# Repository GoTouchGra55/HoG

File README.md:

# HoG FC

This repository includes the custom flight controller, a PDU, and a telemetry unit that is to be used in the drone.

# Overviews

Hand of God flight controller is a custom STM32-based drone flight computer intended to be deployed for humanitarian aid missions.

See [FC Schematics](Kicad/FC/HoG.pdf)
See [Telemetry Schematics](Kicad/Telemetry/HoG_Telemetry.pdf)

## Routing

# Features

## Core

- STM32H743 Cortex-M7 MCU
- Up to 480 MHz CPU clock
- MicroSD storage
- SWD debugging
- USB-C
- Barometer
- Gyroscope & Accelerometer
- GPS/GNSS

## Power

The flight controller board provides dedicated:

- 22.2 V rail (6s nominal)
- 5 V rail
- 3.3 V rail

## Rough BOM

| #   | Item           |        Cost | Supplier    |
| --- | -------------- | ----------: | ----------- |
| 1   | PCBs           |     $299.96 | JLCPCB      |
| 2   | SMD Resistors  |       $8.35 | Daraz Nepal |
| 3   | SMD Capacitors |       $7.98 | Daraz Nepal |
|     | **Total**      | **$316.29** |             |

# Authors 👥

Shaurya (Electronics)  
Contact: [E-mail](shauryatamang.dev@gmail.com)

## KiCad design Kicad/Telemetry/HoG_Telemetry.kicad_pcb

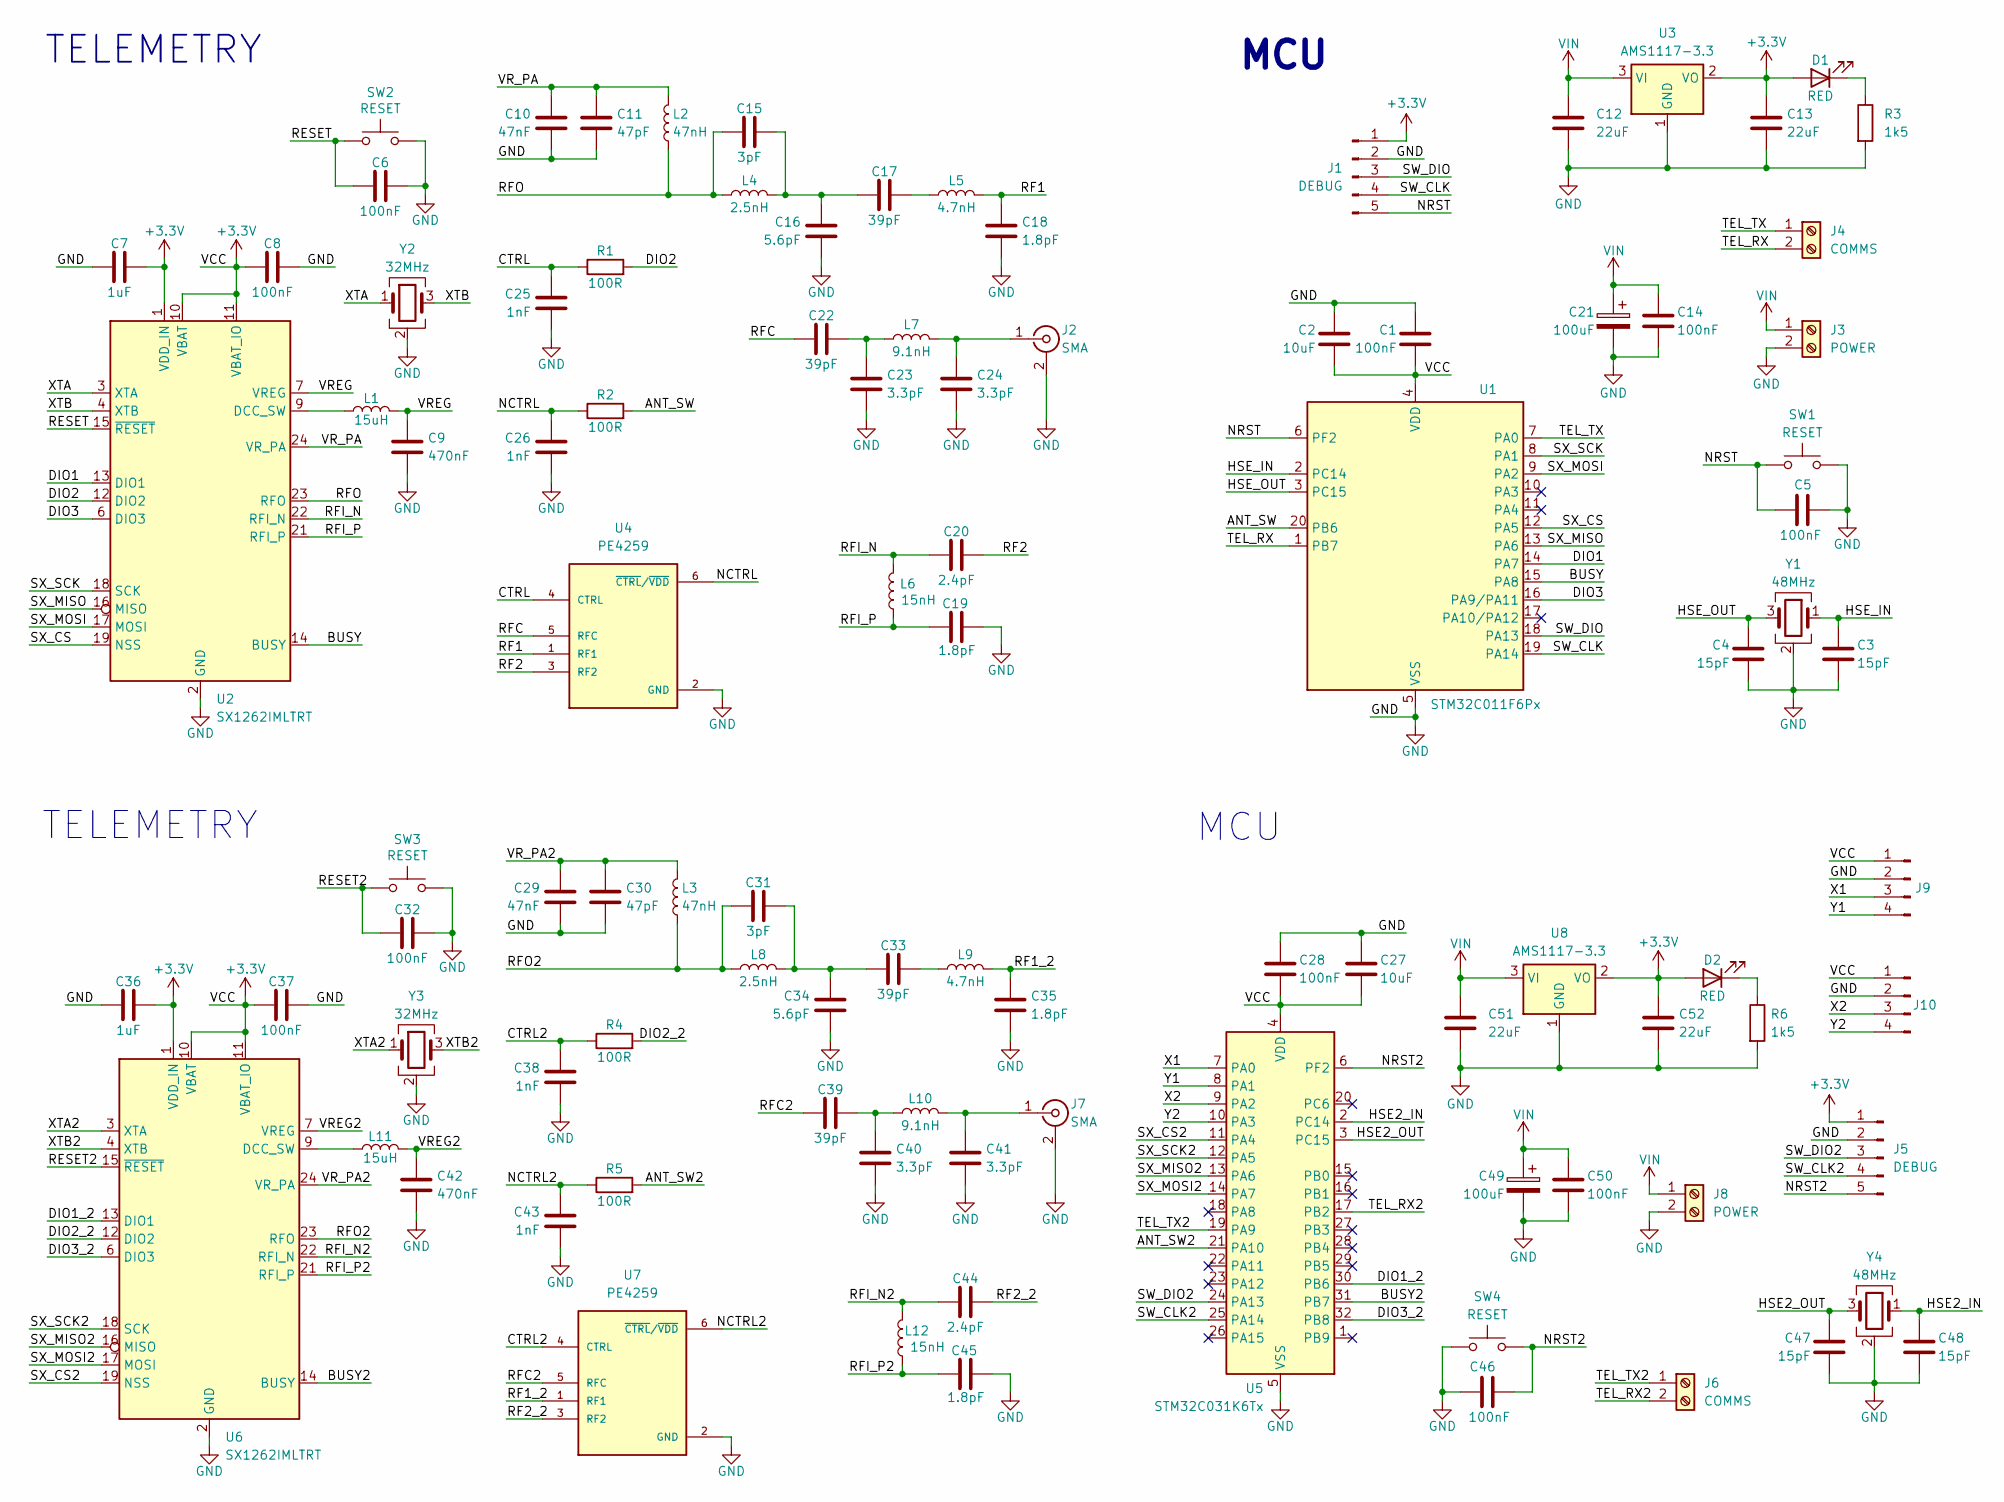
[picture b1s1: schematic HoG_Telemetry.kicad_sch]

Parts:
C1, C5, C6, C8, C14, C28, C32, C37, C46, C50: 100nF; C_0402_1005Metric
C2, C27: 10uF; C_0603_1608Metric
C3, C4, C47, C48: 15pF; C_0402_1005Metric
C7, C36: 1uF; C_0603_1608Metric
C9, C42: 470nF; C_0402_1005Metric
C10, C29: 47nF; C_0402_1005Metric
C11, C30: 47pF; C_0402_1005Metric
C12, C13, C51, C52: 22uF; C_0805_2012Metric
C15, C31: 3pF; C_0402_1005Metric
C16, C34: 5.6pF; C_0402_1005Metric
C17, C22, C33, C39: 39pF; C_0402_1005Metric
C18, C19, C35, C45: 1.8pF; C_0402_1005Metric
C20, C44: 2.4pF; C_0402_1005Metric
C21, C49: 100uF; C_0603_1608Metric
C23, C24, C40, C41: 3.3pF; C_0402_1005Metric
C25, C26, C38, C43: 1nF; C_0402_1005Metric
D1, D2: RED; LED_0603_1608Metric
J1, J5: DEBUG; PinHeader_1x05_P2.54mm_Horizontal
J2, J7: SMA; SMA_Amphenol_132134-10_Vertical
J3, J8: POWER; PinHeader_1x02_P2.54mm_Horizontal
J4, J6: COMMS; PinHeader_1x02_P2.54mm_Horizontal
J9, J10: Conn_01x04_Pin; JST_EH_B4B-EH-A_1x04_P2.50mm_Vertical
L1, L11: 15uH; L_0805_2012Metric
L2, L3: 47nH; L_0402_1005Metric
L4, L8: 2.5nH; L_0402_1005Metric
L5, L9: 4.7nH; L_0402_1005Metric
L6, L12: 15nH; L_0402_1005Metric
L7, L10: 9.1nH; L_0402_1005Metric
R1, R2, R4, R5: 100R; R_0402_1005Metric
R3, R6: 1k5; R_0402_1005Metric
SW1, SW2, SW3, SW4: RESET; SW_Push_SPST_NO_Alps_SKRK
U1: STM32C011F6Px; TSSOP-20_4.4x6.5mm_P0.65mm
U2, U6: SX1262IMLTRT; QFN-24-1EP_4x4mm_P0.5mm_EP2.6x2.6mm
U3, U8: AMS1117-3.3; SOT-223-3_TabPin2
U4, U7: PE4259; SOT65P215X110-6N
U5: STM32C031K6Tx; LQFP-32_7x7mm_P0.8mm
Y1, Y4: 48MHz; Crystal_SMD_3225-4Pin_3.2x2.5mm
Y2, Y3: 32MHz; Crystal_SMD_3225-4Pin_3.2x2.5mm

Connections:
+3.3V: C1.2, C2.2, C7.2, C8.1, C13.1, C27.2, C28.2, C36.2, C37.1, C52.1, D1.2 (A), D2.2 (A), J1.1, J5.1, J9.1, J10.1, U1.4 (VDD), U2.1 (VDD_IN), U2.10 (VBAT), U2.11 (VBAT_IO), U3.2 (VO), U5.4 (VDD), U6.1 (VDD_IN), U6.10 (VBAT), U6.11 (VBAT_IO), U8.2 (VO)
/ANT_SW: R2.2, U1.20 (PB6)
/ANT_SW2: R5.2, U5.21 (PA10)
/BUSY: U1.15 (PA8), U2.14 (BUSY)
/BUSY2: U5.31 (PB7), U6.14 (BUSY)
/CTRL: C25.1, R1.1, U4.4 (CTRL)
/CTRL2: C38.1, R4.1, U7.4 (CTRL)
/DIO1: U1.14 (PA7), U2.13 (DIO1)
/DIO1_2: U5.30 (PB6), U6.13 (DIO1)
/DIO2: R1.2, U2.12 (DIO2)
/DIO2_2: R4.2, U6.12 (DIO2)
/DIO3: U1.16 (PA9/PA11), U2.6 (DIO3)
/DIO3_2: U5.32 (PB8), U6.6 (DIO3)
/HSE2_IN: C48.1, U5.2 (PC14), Y4.1
/HSE2_OUT: C47.1, U5.3 (PC15), Y4.3
/HSE_IN: C3.1, U1.2 (PC14), Y1.1
/HSE_OUT: C4.1, U1.3 (PC15), Y1.3
/NCTRL: C26.1, R2.1, U4.6 (~CTRL/~VDD)
/NCTRL2: C43.1, R5.1, U7.6 (~CTRL/~VDD)
/NRST: C5.2, J1.5, SW1.2, U1.6 (PF2)
/NRST2: C46.2, J5.5, SW4.2, U5.6 (PF2)
/RESET: C6.2, SW2.2, U2.15 (~RESET)
/RESET2: C32.2, SW3.2, U6.15 (~RESET)
/RF1: C18.1, L5.2, U4.1 (RF1)
/RF1_2: C35.1, L9.2, U7.1 (RF1)
/RF2: C20.2, U4.3 (RF2)
/RF2_2: C44.2, U7.3 (RF2)
/RFC: C22.1, U4.5 (RFC)
/RFC2: C39.1, U7.5 (RFC)
/RFI_N: C20.1, L6.2, U2.22 (RFI_N)
/RFI_N2: C44.1, L12.2, U6.22 (RFI_N)
/RFI_P: C19.1, L6.1, U2.21 (RFI_P)
/RFI_P2: C45.1, L12.1, U6.21 (RFI_P)
/RFO: C15.1, L2.1, L4.1, U2.23 (RFO)
/RFO2: C31.1, L3.1, L8.1, U6.23 (RFO)
/SW_CLK: J1.4, U1.19 (PA14)
/SW_CLK2: J5.4, U5.25 (PA14)
/SW_DIO: J1.3, U1.18 (PA13)
/SW_DIO2: J5.3, U5.24 (PA13)
/SX_CS: U1.12 (PA5), U2.19 (NSS)
/SX_CS2: U5.11 (PA4), U6.19 (NSS)
/SX_MISO: U1.13 (PA6), U2.16 (MISO)
/SX_MISO2: U5.13 (PA6), U6.16 (MISO)
/SX_MOSI: U1.9 (PA2), U2.17 (MOSI)
/SX_MOSI2: U5.14 (PA7), U6.17 (MOSI)
/SX_SCK: U1.8 (PA1), U2.18 (SCK)
/SX_SCK2: U5.12 (PA5), U6.18 (SCK)
/TEL_RX: J4.2, U1.1 (PB7)
/TEL_RX2: J6.2, U5.17 (PB2)
/TEL_TX: J4.1, U1.7 (PA0)
/TEL_TX2: J6.1, U5.19 (PA9)
/VREG: C9.1, L1.2, U2.7 (VREG)
/VREG2: C42.1, L11.2, U6.7 (VREG)
/VR_PA: C10.1, C11.1, L2.2, U2.24 (VR_PA)
/VR_PA2: C29.1, C30.1, L3.2, U6.24 (VR_PA)
/X1: J9.3, U5.7 (PA0)
/X2: J10.3, U5.9 (PA2)
/XTA: U2.3 (XTA), Y2.1
/XTA2: U6.3 (XTA), Y3.1
/XTB: U2.4 (XTB), Y2.3
/XTB2: U6.4 (XTB), Y3.3
/Y1: J9.4, U5.8 (PA1)
/Y2: J10.4, U5.10 (PA3)
GND: C1.1, C2.1, C3.2, C4.2, C5.1, C6.1, C7.1, C8.2, C9.2, C10.2, C11.2, C12.2, C13.2, C14.2, C16.2, C18.2, C19.2, C21.2, C23.2, C24.2, C25.2, C26.2, C27.1, C28.1, C29.2, C30.2, C32.1, C34.2, C35.2, C36.1, C37.2, C38.2, C40.2, C41.2, C42.2, C43.2, C45.2, C46.1, C47.2, C48.2, C49.2, C50.2, C51.2, C52.2, J1.2, J2.2 (Ext), J3.2, J5.2, J7.2 (Ext), J8.2, J9.2, J10.2, R3.2, R6.2, SW1.1, SW2.1, SW3.1, SW4.1, U1.5 (VSS), U2.2 (GND), U2.5 (GND), U2.8 (GND), U2.20 (GND), U2.25 (GND), U3.1 (GND), U4.2 (GND), U5.5 (VSS), U6.2 (GND), U6.5 (GND), U6.8 (GND), U6.20 (GND), U6.25 (GND), U7.2 (GND), U8.1 (GND), Y1.2 (G), Y1.4 (G), Y2.2 (G), Y2.4 (G), Y3.2 (G), Y3.4 (G), Y4.2 (G), Y4.4 (G)
unnamed: C15.2, C16.1, C17.1, L4.2
unnamed: C17.2, L5.1
unnamed: C22.2, C23.1, L7.1
unnamed: C31.2, C33.1, C34.1, L8.2
unnamed: C33.2, L9.1
unnamed: C39.2, C40.1, L10.1
unnamed: D1.1 (K), R3.1
unnamed: D2.1 (K), R6.1
unnamed: C24.1, J2.1 (In), L7.2
unnamed: C41.1, J7.1 (In), L10.2
unnamed: L1.1, U2.9 (DCC_SW)
unnamed: L11.1, U6.9 (DCC_SW)
VIN: C12.1, C14.1, C21.1, C49.1, C50.1, C51.1, J3.1, J8.1, U3.3 (VI), U8.3 (VI)

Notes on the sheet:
MCU
TELEMETRY

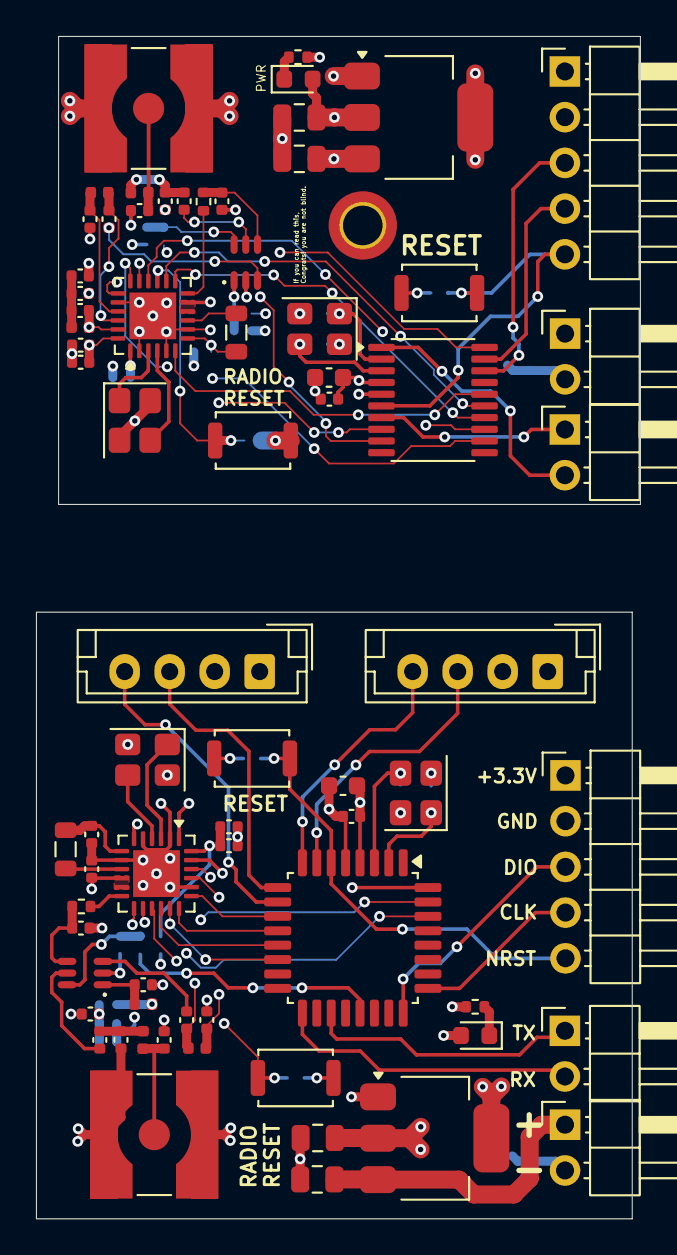
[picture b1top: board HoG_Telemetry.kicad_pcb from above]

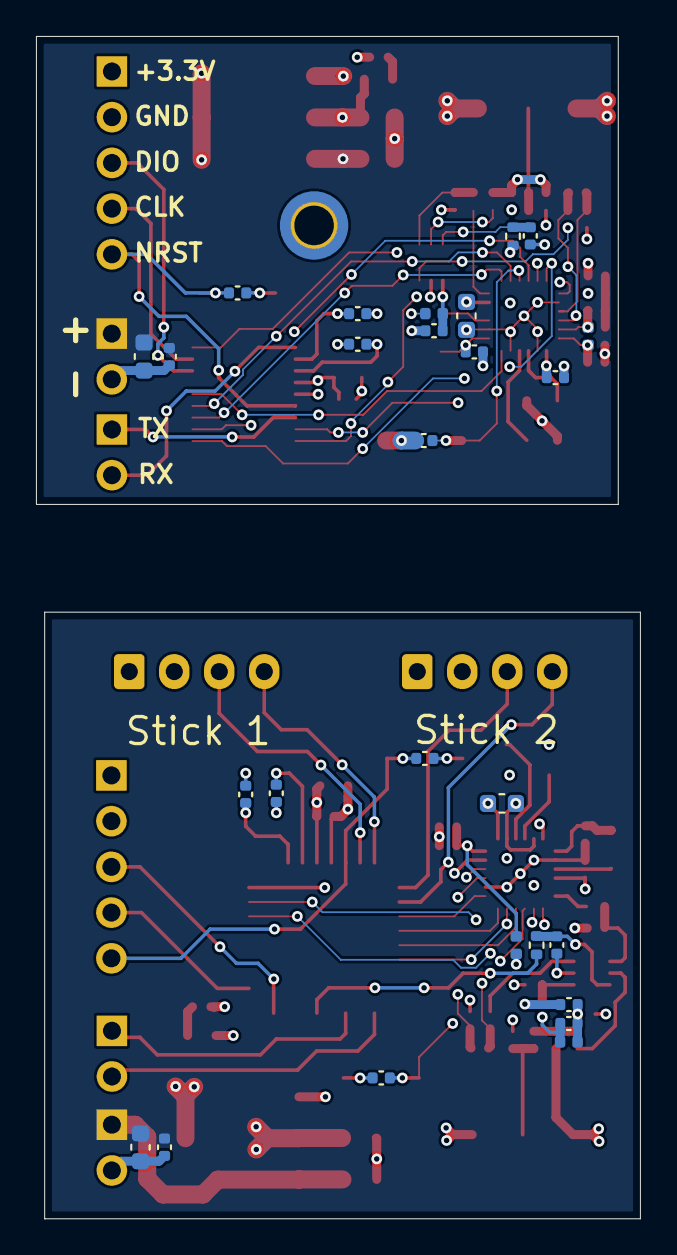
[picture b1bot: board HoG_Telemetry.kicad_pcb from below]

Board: 4 copper layers, 33.6 x 65.7 mm, 98 parts (27 on the bottom side), 77 nets.

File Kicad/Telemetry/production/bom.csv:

Designator,Footprint,Quantity,Value,LCSC Part #
"C1, C14, C28, C32, C37, C46, C5, C50, C6, C8",0402,10,100nF,
"C10, C29",0402,2,47nF,
"C11, C30",0402,2,47pF,
"C12, C13, C51, C52",0805,4,22uF,
"C15, C31",0402,2,3pF,
"C16, C34",0402,2,5.6pF,
"C17, C22, C33, C39",0402,4,39pF,
"C18, C19, C35, C45",0402,4,1.8pF,
"C2, C27",0603,2,10uF,
"C20, C44",0402,2,2.4pF,
"C21, C49",0603,2,100uF,
"C23, C24, C40, C41",0402,4,3.3pF,
"C25, C26, C38, C43",0402,4,1nF,
"C3, C4, C47, C48",0402,4,15pF,
"C36, C7",0603,2,1uF,
"C42, C9",0402,2,470nF,
"D1, D2",0603,2,RED,
"J1, J5",PinHeader_1x05_P2.54mm_Horizontal,2,DEBUG,
"J10, J9",JST_EH_B4B-EH-A_1x04_P2.50mm_Vertical,2,Conn_01x04_Pin,
"J2, J7",SMA_Amphenol_132134-10_Vertical,2,SMA,
"J3, J8",PinHeader_1x02_P2.54mm_Horizontal,2,POWER,
"J4, J6",PinHeader_1x02_P2.54mm_Horizontal,2,COMMS,
"L1, L11",0805,2,15uH,
"L10, L7",0402,2,9.1nH,
"L12, L6",0402,2,15nH,
"L2, L3",0402,2,47nH,
"L4, L8",0402,2,2.5nH,
"L5, L9",0402,2,4.7nH,
"R1, R2, R4, R5",0402,4,100R,
"R3, R6",0402,2,1k5,
"SW1, SW2, SW3, SW4",SW_Push_SPST_NO_Alps_SKRK,4,RESET,
U1,TSSOP-20_4.4x6.5mm_P0.65mm,1,STM32C011F6Px,
"U2, U6",QFN-24-1EP_4x4mm_P0.5mm_EP2.6x2.6mm,2,SX1262IMLTRT,
"U3, U8",SOT-223-3_TabPin2,2,AMS1117-3.3,
"U4, U7",SOT65P215X110-6N,2,PE4259,
U5,LQFP-32_7x7mm_P0.8mm,1,STM32C031K6Tx,
"Y1, Y4",Crystal_SMD_3225-4Pin_3.2x2.5mm,2,48MHz,
"Y2, Y3",Crystal_SMD_3225-4Pin_3.2x2.5mm,2,32MHz,

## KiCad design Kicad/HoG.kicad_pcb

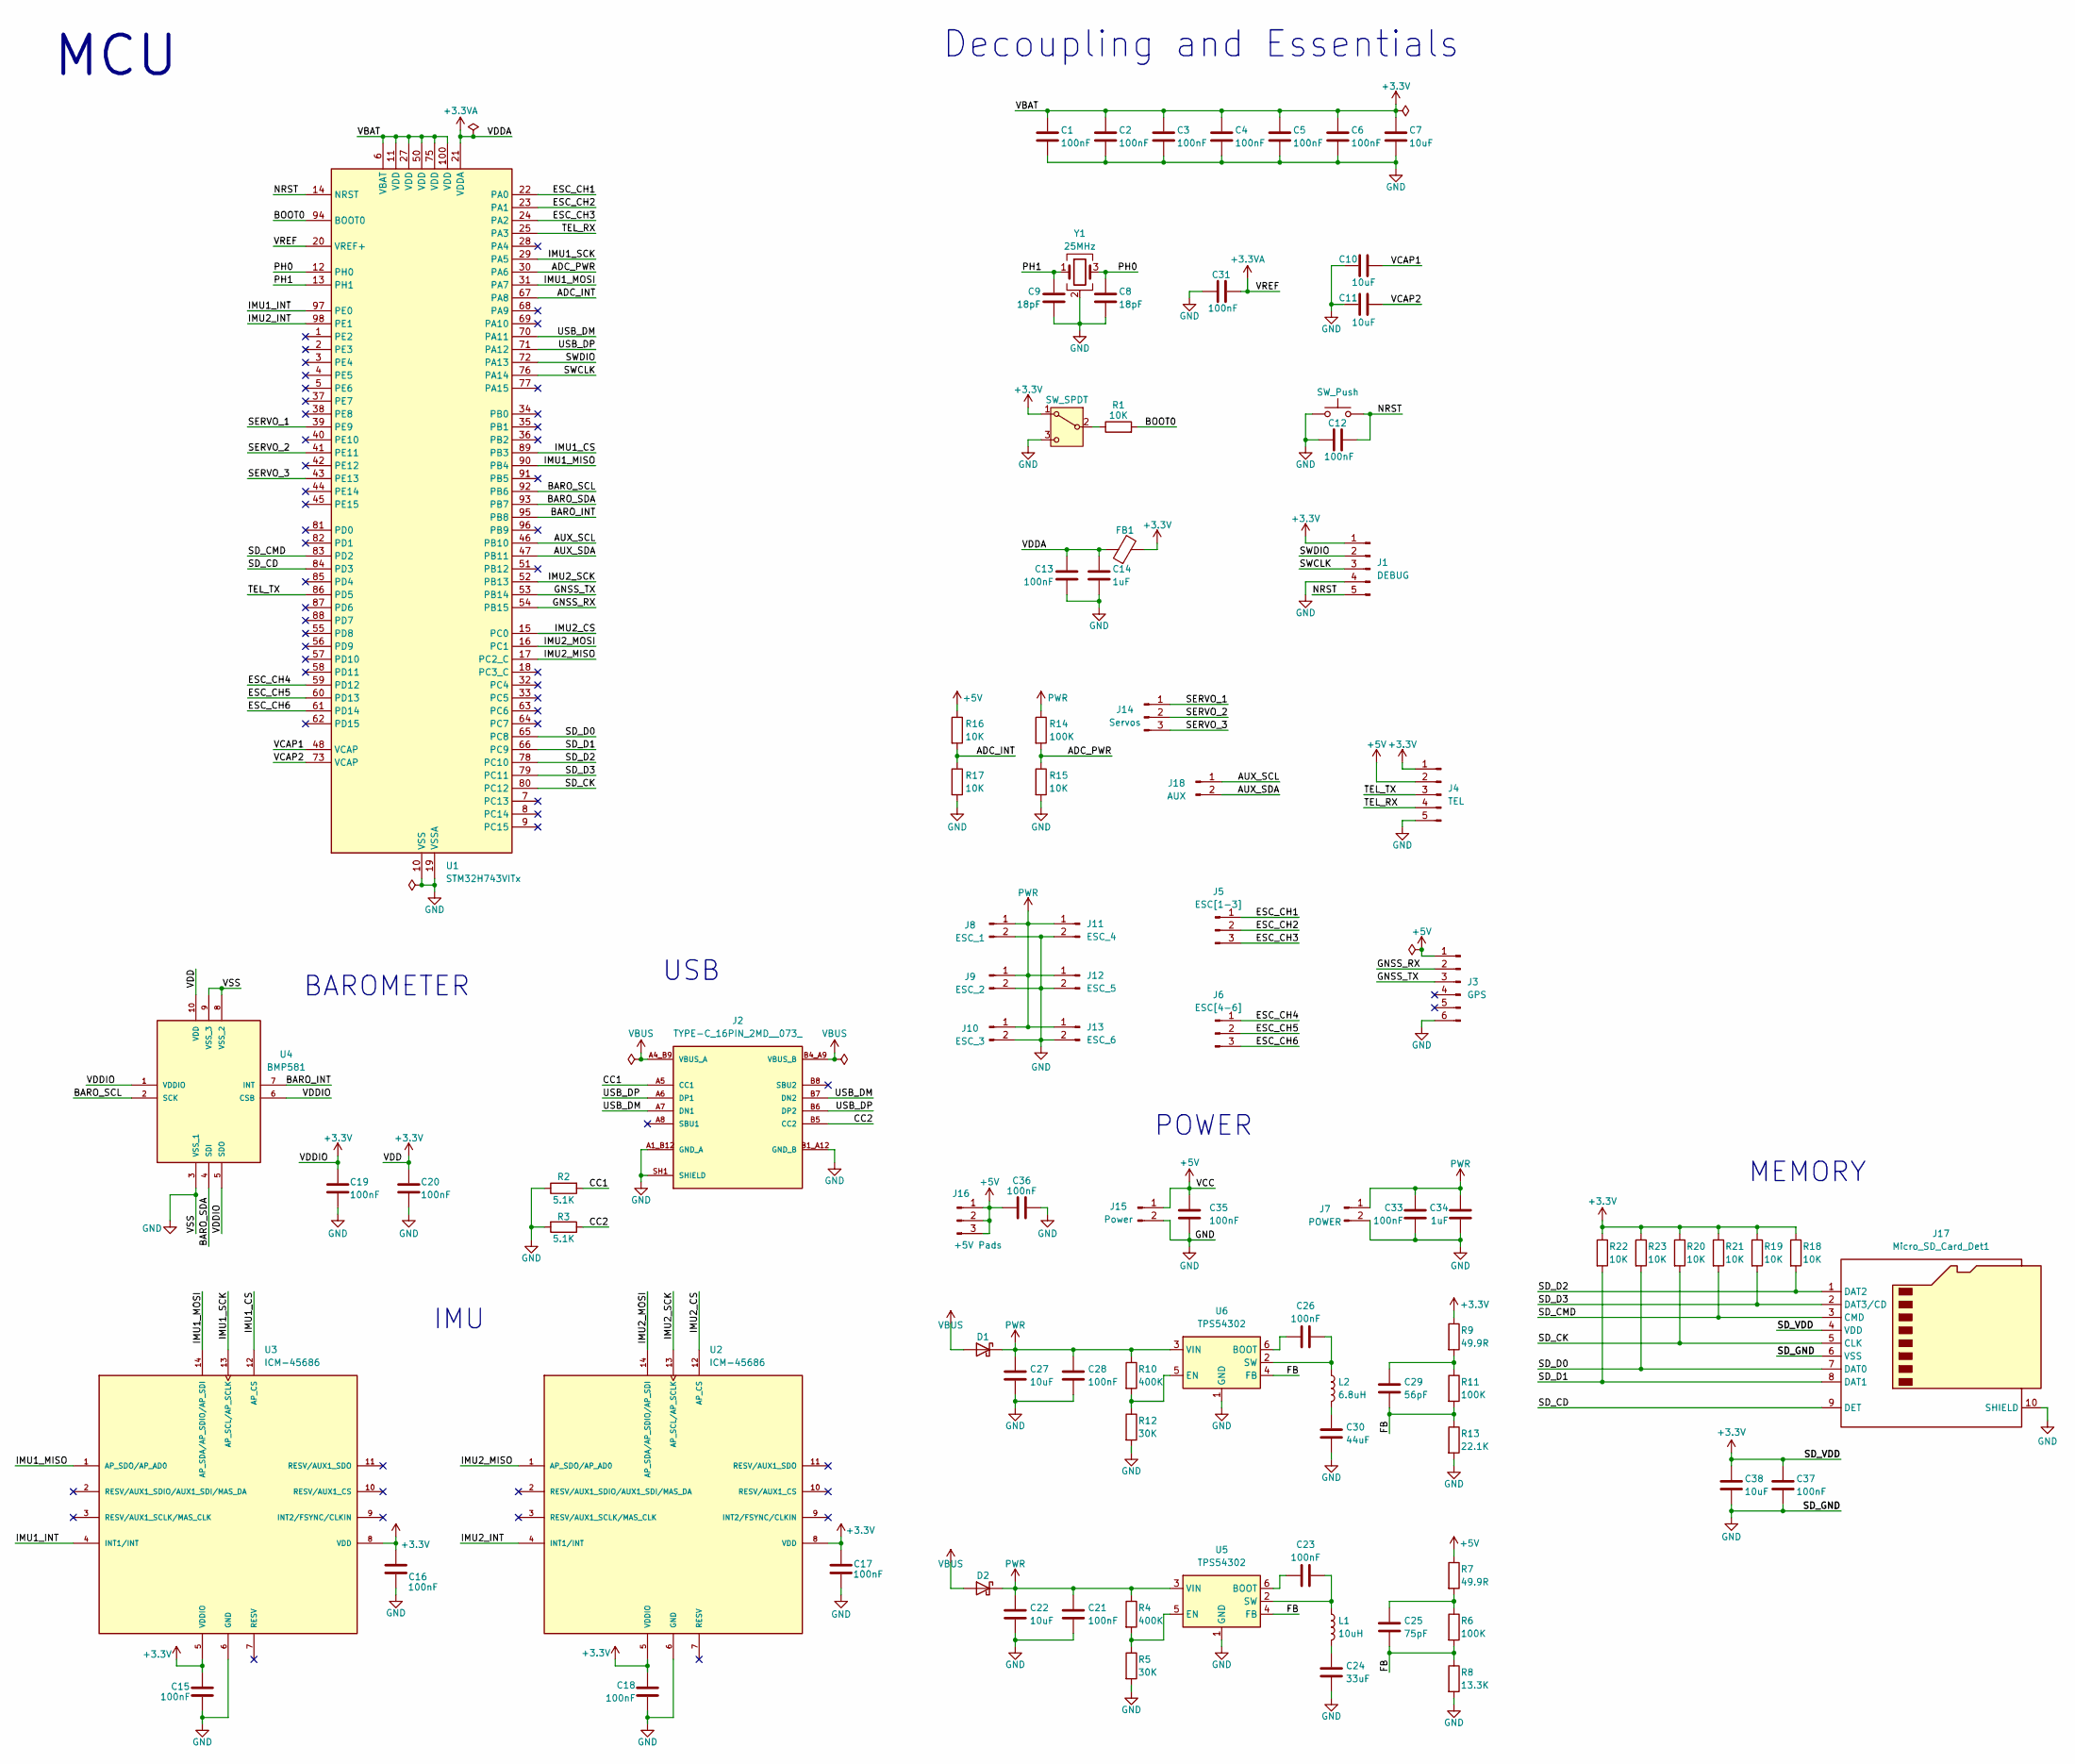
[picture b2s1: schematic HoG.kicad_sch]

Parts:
C1, C2, C3, C4, C5, C6, C12, C13, C15, C16, C17, C18, C19, C20, C21, C23, C26, C28, C31, C33, C35, C36, C37: 100nF; C_0402_1005Metric
C7, C10, C11, C22, C27, C38: 10uF; C_0603_1608Metric
C8, C9: 18pF; C_0402_1005Metric
C14, C34: 1uF; C_0603_1608Metric
C24: 33uF; C_0603_1608Metric
C25: 75pF; C_0402_1005Metric
C29: 56pF; C_0402_1005Metric
C30: 44uF; C_0603_1608Metric
D1, D2: D_Schottky; D_SOD-123
FB1: FerriteBead; C_0603_1608Metric
J1: DEBUG; JST_EH_S5B-EH_1x05_P2.50mm_Horizontal
J2: TYPE-C_16PIN_2MD__073_; SHOUHAN_TYPE-C_16PIN_2MD__073_; PARTREV A
J3: GPS; JST_EH_S6B-EH_1x06_P2.50mm_Horizontal
J4: TEL; JST_EH_S5B-EH_1x05_P2.50mm_Horizontal
J5: ESC[1-3]; SolderWire-0.5sqmm_1x03_P4.6mm_D0.9mm_OD2.1mm
J6: ESC[4-6]; SolderWire-0.5sqmm_1x03_P4.6mm_D0.9mm_OD2.1mm
J7: POWER; AMASS_XT60-M_1x02_P7.20mm_Vertical
J8: ESC_1; SolderWire-0.5sqmm_1x02_P4.8mm_D0.9mm_OD2.3mm
J9: ESC_2; SolderWire-0.5sqmm_1x02_P4.8mm_D0.9mm_OD2.3mm
J10: ESC_3; SolderWire-0.5sqmm_1x02_P4.8mm_D0.9mm_OD2.3mm
J11: ESC_4; SolderWire-0.5sqmm_1x02_P4.8mm_D0.9mm_OD2.3mm
J12: ESC_5; SolderWire-0.5sqmm_1x02_P4.8mm_D0.9mm_OD2.3mm
J13: ESC_6; SolderWire-0.5sqmm_1x02_P4.8mm_D0.9mm_OD2.3mm
J14: Servos; SolderWire-0.5sqmm_1x03_P4.6mm_D0.9mm_OD2.1mm
J15: Power; PinHeader_1x02_P2.54mm_Horizontal
J16: +5V Pads; PinHeader_1x03_P2.54mm_Vertical
J17: Micro_SD_Card_Det1; microSD_HC_Wuerth
J18: AUX; PinHeader_1x02_P2.54mm_Horizontal
L1: 10uH; L_Cenker_CKCS3012
L2: 6.8uH; L_Cenker_CKCS4030
R1, R15, R16, R17, R18, R19, R20, R21, R22, R23: 10K; R_0402_1005Metric
R2, R3: 5.1K; R_0402_1005Metric
R4, R10: 400K; R_0603_1608Metric
R5, R12: 30K; R_0603_1608Metric
R6, R11, R14: 100K; R_0603_1608Metric
R7, R9: 49.9R; R_0402_1005Metric
R8: 13.3K; R_0402_1005Metric
R13: 22.1K; R_0603_1608Metric
SW1: SW_SPDT; SW_SPDT_PCM12
SW2: SW_Push; SW_Push_SPST_NO_Alps_SKRK
U1: STM32H743VITx; LQFP-100_14x14mm_P0.5mm
U2, U3: ICM-45686; IC_ICM-45686
U4: BMP581; Manufacturer_Part_Number BMP581
U5, U6: TPS54302; SOT-23-6
Y1: 25MHz; Crystal_SMD_3225-4Pin_3.2x2.5mm

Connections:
+3.3V: C1.1, C2.1, C3.1, C4.1, C5.1, C6.1, C7.1, C15.2, C16.2, C17.2, C18.1, C19.1, C20.1, C37.1, C38.1, FB1.2, J1.1, J4.1, J17.4 (VDD), R9.1, R18.1, R19.1, R20.1, R21.1, R22.1, R23.1, SW1.1 (A), U1.6 (VBAT), U1.11 (VDD), U1.27 (VDD), U1.50 (VDD), U1.75 (VDD), U1.100 (VDD), U2.5 (VDDIO), U2.8 (VDD), U3.5 (VDDIO), U3.8 (VDD), U4.1 (VDDIO), U4.5 (SDO), U4.6 (CSB), U4.10 (VDD)
+3.3VA: C13.1, C14.1, C31.2, FB1.1, U1.20 (VREF+), U1.21 (VDDA)
+5V: C35.1, C36.1, J3.1, J4.2, J15.1, J16.1, J16.2, J16.3, R7.1, R16.1
/ADC_INT: R16.2, R17.1, U1.67 (PA8)
/ADC_PWR: R14.2, R15.1, U1.30 (PA6)
/AUX_SCL: J18.1, U1.46 (PB10)
/AUX_SDA: J18.2, U1.47 (PB11)
/BARO_INT: U1.95 (PB8), U4.7 (INT)
/BARO_SCL: U1.92 (PB6), U4.2 (SCK)
/BARO_SDA: U1.93 (PB7), U4.4 (SDI)
/BOOT0: R1.2, U1.94 (BOOT0)
/CC1: J2.A5 (CC1), R2.2
/CC2: J2.B5 (CC2), R3.1
/ESC_CH1: J5.1, U1.22 (PA0)
/ESC_CH2: J5.2, U1.23 (PA1)
/ESC_CH3: J5.3, U1.24 (PA2)
/ESC_CH4: J6.1, U1.59 (PD12)
/ESC_CH5: J6.2, U1.60 (PD13)
/ESC_CH6: J6.3, U1.61 (PD14)
/FB: C25.2, C29.2, R6.2, R8.1, R11.2, R13.1, U5.4 (FB), U6.4 (FB)
/GNSS_RX: J3.2, U1.54 (PB15)
/GNSS_TX: J3.3, U1.53 (PB14)
/IMU1_CS: U1.89 (PB3), U3.12 (AP_CS)
/IMU1_INT: U1.97 (PE0), U3.4 (INT1/INT)
/IMU1_MISO: U1.90 (PB4), U3.1 (AP_SDO/AP_AD0)
/IMU1_MOSI: U1.31 (PA7), U3.14 (AP_SDA/AP_SDIO/AP_SDI)
/IMU1_SCK: U1.29 (PA5), U3.13 (AP_SCL/AP_SCLK)
/IMU2_CS: U1.15 (PC0), U2.12 (AP_CS)
/IMU2_INT: U1.98 (PE1), U2.4 (INT1/INT)
/IMU2_MISO: U1.17 (PC2_C), U2.1 (AP_SDO/AP_AD0)
/IMU2_MOSI: U1.16 (PC1), U2.14 (AP_SDA/AP_SDIO/AP_SDI)
/IMU2_SCK: U1.52 (PB13), U2.13 (AP_SCL/AP_SCLK)
/NRST: C12.2, J1.5, SW2.2, U1.14 (NRST)
/PH0: C8.1, U1.12 (PH0), Y1.3
/PH1: C9.1, U1.13 (PH1), Y1.1
/SD_CD: J17.9 (DET), U1.84 (PD3)
/SD_CK: J17.5 (CLK), R20.2, U1.80 (PC12)
/SD_CMD: J17.3 (CMD), R21.2, U1.83 (PD2)
/SD_D0: J17.7 (DAT0), R23.2, U1.65 (PC8)
/SD_D1: J17.8 (DAT1), R22.2, U1.66 (PC9)
/SD_D2: J17.1 (DAT2), R18.2, U1.78 (PC10)
/SD_D3: J17.2 (DAT3/CD), R19.2, U1.79 (PC11)
/SERVO_1: J14.1, U1.39 (PE9)
/SERVO_2: J14.2, U1.41 (PE11)
/SERVO_3: J14.3, U1.43 (PE13)
/SWCLK: J1.3, U1.76 (PA14)
/SWDIO: J1.2, U1.72 (PA13)
/TEL_RX: J4.4, U1.25 (PA3)
/TEL_TX: J4.3, U1.86 (PD5)
/USB_DM: J2.A7 (DN1), J2.B7 (DN2), U1.70 (PA11)
/USB_DP: J2.A6 (DP1), J2.B6 (DP2), U1.71 (PA12)
/VCAP1: C10.2, U1.48 (VCAP)
/VCAP2: C11.1, U1.73 (VCAP)
GND: C1.2, C2.2, C3.2, C4.2, C5.2, C6.2, C7.2, C8.2, C9.2, C10.1, C11.2, C12.1, C13.2, C14.2, C15.1, C16.1, C17.1, C18.2, C19.2, C20.2, C21.2, C22.2, C24.2, C27.2, C28.2, C30.2, C31.1, C33.2, C34.2, C35.2, C36.2, C37.2, C38.2, J1.4, J2.A1_B12 (GND_A), J2.B1_A12 (GND_B), J2.SH1 (SHIELD), J2.SH2 (SHIELD), J2.SH3 (SHIELD), J2.SH4 (SHIELD), J3.6, J4.5, J7.2, J8.2, J9.2, J10.2, J11.2, J12.2, J13.2, J15.2, J17.6 (VSS), J17.10 (SHIELD), R2.1, R3.2, R5.2, R8.2, R12.2, R13.2, R15.2, R17.2, SW1.3 (C), SW2.1, U1.10 (VSS), U1.19 (VSSA), U1.26 (VSS), U1.49 (VSS), U1.74 (VSS), U1.99 (VSS), U2.6 (GND), U3.6 (GND), U4.3 (VSS_1), U4.8 (VSS_2), U4.9 (VSS_3), U5.1 (GND), U6.1 (GND), Y1.2 (G), Y1.4 (G); also elsewhere on the board
unnamed: C24.1, L1.2
unnamed: C25.1, R6.1, R7.2
unnamed: C29.1, R9.2, R11.1
unnamed: C30.1, L2.2
unnamed: R1.1, SW1.2 (B)
unnamed: C23.1, U5.6 (BOOT)
unnamed: R4.2, R5.1, U5.5 (EN)
unnamed: C23.2, L1.1, U5.2 (SW)
unnamed: C26.1, U6.6 (BOOT)
unnamed: R10.2, R12.1, U6.5 (EN)
unnamed: C26.2, L2.1, U6.2 (SW)
PWR: C21.1, C22.1, C27.1, C28.1, C33.1, C34.1, D1.1 (K), D2.1 (K), J7.1, J8.1, J9.1, J10.1, J11.1, J12.1, J13.1, R4.1, R10.1, R14.1, U5.3 (VIN), U6.3 (VIN); also elsewhere on the board
VBUS: D1.2 (A), D2.2 (A), J2.A4_B9 (VBUS_A), J2.B4_A9 (VBUS_B)

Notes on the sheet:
IMU
USB
MEMORY
MCU
BAROMETER
POWER
Decoupling and Essentials

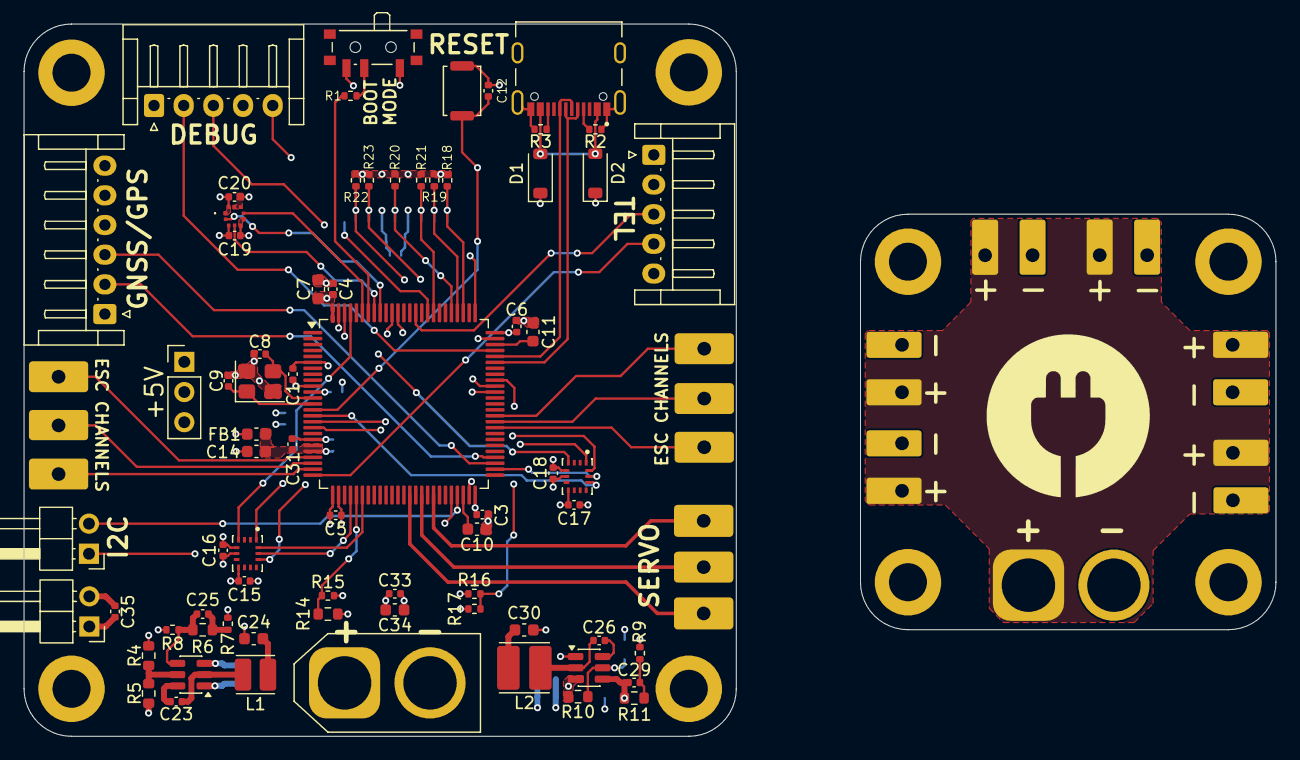
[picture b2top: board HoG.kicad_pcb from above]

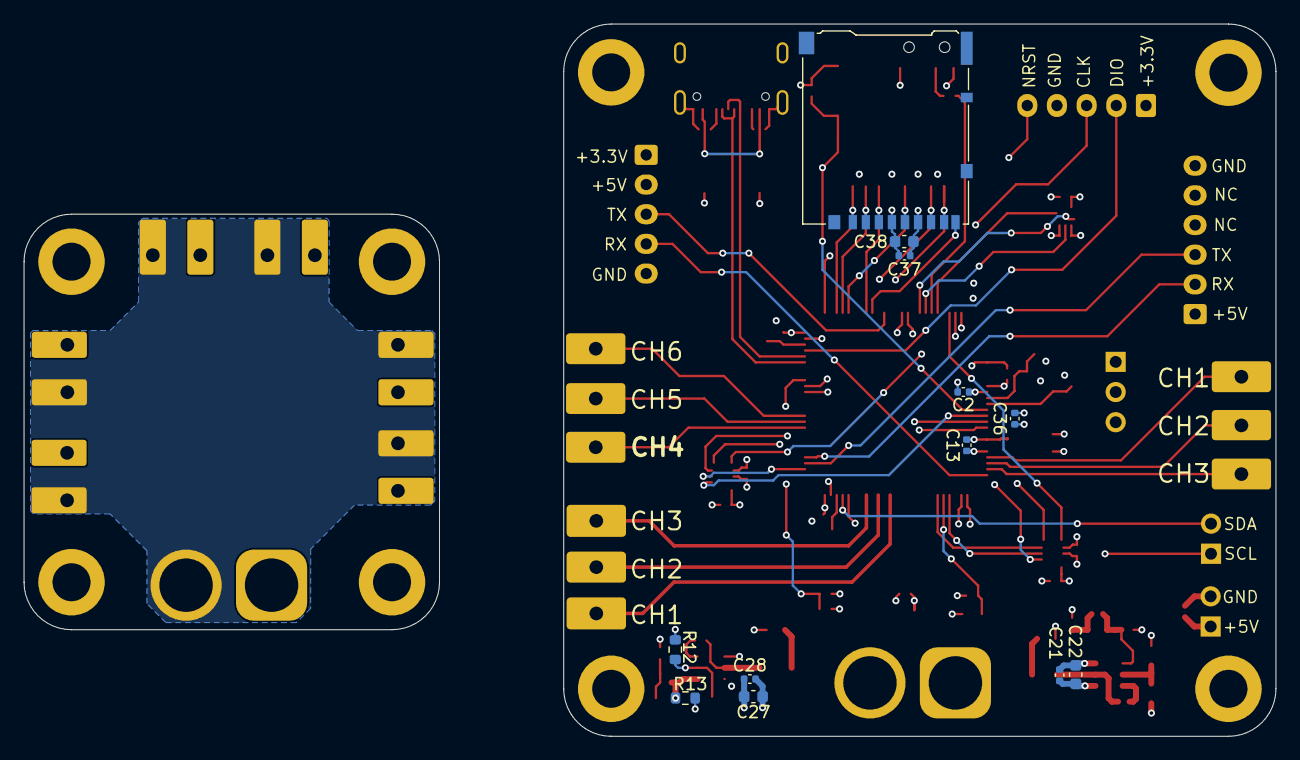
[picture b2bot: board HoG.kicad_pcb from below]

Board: 6 copper layers, 60.0 x 60.0 mm, 93 parts (12 on the bottom side), 67 nets.

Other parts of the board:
J7#2: POWER; AMASS_XT60-M_1x02_P7.20mm_Vertical

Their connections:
GND: J7#2.2; also elsewhere on the board
PWR: J7#2.1; also elsewhere on the board

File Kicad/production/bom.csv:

Designator,Footprint,Quantity,Value,LCSC Part #
"C1, C12, C13, C15, C16, C17, C18, C19, C2, C20, C21, C23, C26, C28, C3, C31, C33, C35, C36, C37, C4, C5, C6",0402,23,100nF,
"C10, C11, C22, C27, C38, C7",0603,6,10uF,
"C14, C34",0603,2,1uF,
C24,0603,1,33uF,
C25,0402,1,75pF,
C29,0402,1,56pF,
C30,0603,1,44uF,
"C8, C9",0402,2,18pF,
"D1, D2",D_SOD-123,2,D_Schottky,
FB1,0603,1,FerriteBead,
J1,JST_EH_S5B-EH_1x05_P2.50mm_Horizontal,1,DEBUG,
J10,SolderWire-0.5sqmm_1x02_P4.8mm_D0.9mm_OD2.3mm,1,ESC_3,
J11,SolderWire-0.5sqmm_1x02_P4.8mm_D0.9mm_OD2.3mm,1,ESC_4,
J12,SolderWire-0.5sqmm_1x02_P4.8mm_D0.9mm_OD2.3mm,1,ESC_5,
J13,SolderWire-0.5sqmm_1x02_P4.8mm_D0.9mm_OD2.3mm,1,ESC_6,
J14,SolderWire-0.5sqmm_1x03_P4.6mm_D0.9mm_OD2.1mm,1,Servos,
J15,PinHeader_1x02_P2.54mm_Horizontal,1,Power,
J16,PinHeader_1x03_P2.54mm_Vertical,1,+5V Pads,
J17,microSD_HC_Hirose_DM3AT-SF-PEJM5,1,Micro_SD_Card_Det1,
J18,PinHeader_1x02_P2.54mm_Horizontal,1,AUX,
J2,SHOUHAN_TYPE-C_16PIN_2MD__073_,1,TYPE-C_16PIN_2MD__073_,
J3,JST_EH_S6B-EH_1x06_P2.50mm_Horizontal,1,GPS,
J4,JST_EH_S5B-EH_1x05_P2.50mm_Horizontal,1,TEL,
J5,SolderWire-0.5sqmm_1x03_P4.6mm_D0.9mm_OD2.1mm,1,ESC[1-3],
J6,SolderWire-0.5sqmm_1x03_P4.6mm_D0.9mm_OD2.1mm,1,ESC[4-6],
"J7_2, J7",AMASS_XT60-M_1x02_P7.20mm_Vertical,2,POWER,
J8,SolderWire-0.5sqmm_1x02_P4.8mm_D0.9mm_OD2.3mm,1,ESC_1,
J9,SolderWire-0.5sqmm_1x02_P4.8mm_D0.9mm_OD2.3mm,1,ESC_2,
L1,L_Cenker_CKCS3012,1,10uH,
L2,L_Cenker_CKCS4030,1,6.8uH,
"R1, R15, R16, R17, R18, R19, R20, R21, R22, R23",0402,10,10K,
"R10, R4",0603,2,400K,
"R11, R14, R6",0603,3,100K,
"R12, R5",0603,2,30K,
R13,0603,1,22.1K,
"R2, R3",0402,2,5.1K,
"R7, R9",0402,2,49.9R,
R8,0402,1,13.3K,
SW1,SW_SPDT_PCM12,1,SW_SPDT,
SW2,SW_Push_SPST_NO_Alps_SKRK,1,SW_Push,
U1,LQFP-100_14x14mm_P0.5mm,1,STM32H743VITx,
"U2, U3",IC_ICM-45686,2,ICM-45686,
U4,BMP581,1,BMP581,
"U5, U6",SOT-23-6,2,TPS54302,
Y1,Crystal_SMD_3225-4Pin_3.2x2.5mm,1,25MHz,

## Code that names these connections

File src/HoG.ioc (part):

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Mcu.Name=STM32H743VITx
Mcu.Package=LQFP100
Mcu.UserName=STM32H743VITx
PA0.GPIOParameters=GPIO_Label
PA0.GPIO_Label=ESC_CH1
PA0.Signal=S_TIM2_CH1_ETR
PA1.GPIOParameters=GPIO_Label
PA1.GPIO_Label=ESC_CH2
PA1.Signal=S_TIM2_CH2
PA11.Mode=Host_Only
PA11.Signal=USB_OTG_FS_DM
PA12.Mode=Host_Only
PA12.Signal=USB_OTG_FS_DP
PA13\ (JTMS/SWDIO).Mode=Serial_Wire
PA13\ (JTMS/SWDIO).Signal=DEBUG_JTMS-SWDIO
PA14\ (JTCK/SWCLK).Mode=Serial_Wire
PA14\ (JTCK/SWCLK).Signal=DEBUG_JTCK-SWCLK
PA2.GPIOParameters=GPIO_Label
PA2.GPIO_Label=ESC_CH3
PA2.Signal=S_TIM2_CH3
PA3.GPIOParameters=GPIO_Label
PA3.GPIO_Label=TEL_RX
PA3.Mode=Asynchronous
PA3.Signal=USART2_RX
PA5.GPIOParameters=GPIO_Label
PA5.GPIO_Label=IMU1_SCK
PA5.Mode=Full_Duplex_Master
PA5.Signal=SPI1_SCK
PA6.Signal=ADCx_INP3
PA7.GPIOParameters=GPIO_Label
PA7.GPIO_Label=IMU1_MOSI
PA7.Mode=Full_Duplex_Master
PA7.Signal=SPI1_MOSI
PB10.GPIOParameters=GPIO_Label
PB10.GPIO_Label=AUX_SCL
PB10.Mode=I2C
PB10.Signal=I2C2_SCL
PB11.GPIOParameters=GPIO_Label
PB11.GPIO_Label=AUX_SDA
PB11.Mode=I2C
PB11.Signal=I2C2_SDA
PB13.GPIOParameters=GPIO_Label
PB13.GPIO_Label=IMU2_SCK
PB13.Mode=Full_Duplex_Master
PB13.Signal=SPI2_SCK
PB14.GPIOParameters=GPIO_Label
PB14.GPIO_Label=GNSS_TX
PB14.Mode=Asynchronous
PB14.Signal=USART1_TX
PB15.GPIOParameters=GPIO_Label
PB15.GPIO_Label=GNSS_RX
PB15.Mode=Asynchronous
PB15.Signal=USART1_RX
PB4\ (NJTRST).GPIOParameters=GPIO_Label
PB4\ (NJTRST).GPIO_Label=IMU1_MISO
PB4\ (NJTRST).Mode=Full_Duplex_Master
PB4\ (NJTRST).Signal=SPI1_MISO
PB6.GPIOParameters=GPIO_Label
PB6.GPIO_Label=BARO_SCL
PB6.Mode=I2C
PB6.Signal=I2C1_SCL
PB7.GPIOParameters=GPIO_Label
PB7.GPIO_Label=BARO_SDA
PB7.Mode=I2C
PB7.Signal=I2C1_SDA
PC1.GPIOParameters=GPIO_Label
PC1.GPIO_Label=IMU2_MOSI
PC1.Mode=Full_Duplex_Master
PC1.Signal=SPI2_MOSI
PC10.Mode=SD_4_bits_Wide_bus
PC10.Signal=SDMMC1_D2
PC11.Mode=SD_4_bits_Wide_bus
PC11.Signal=SDMMC1_D3
PC12.Mode=SD_4_bits_Wide_bus
PC12.Signal=SDMMC1_CK
PC2_C.GPIOParameters=GPIO_Label
PC2_C.GPIO_Label=IMU2_MISO
PC2_C.Mode=Full_Duplex_Master
PC2_C.Signal=SPI2_MISO
PC4.Signal=ADCx_INP4
PC8.Mode=SD_4_bits_Wide_bus
PC8.Signal=SDMMC1_D0
PC9.Mode=SD_4_bits_Wide_bus
PC9.Signal=SDMMC1_D1
PD12.GPIOParameters=GPIO_Label
PD12.GPIO_Label=ESC_CH4
PD12.Signal=S_TIM4_CH1
PD13.GPIOParameters=GPIO_Label
PD13.GPIO_Label=ESC_CH5
PD13.Signal=S_TIM4_CH2
PD14.GPIOParameters=GPIO_Label
PD14.GPIO_Label=ESC_CH6
PD14.Signal=S_TIM4_CH3
PD2.Mode=SD_4_bits_Wide_bus
PD2.Signal=SDMMC1_CMD
PD5.GPIOParameters=GPIO_Label
PD5.GPIO_Label=TEL_TX
PD5.Mode=Asynchronous
PD5.Signal=USART2_TX
PE11.Signal=S_TIM1_CH2
PE13.Signal=S_TIM1_CH3
PE9.Signal=S_TIM1_CH1
PH0-OSC_IN\ (PH0).Mode=HSE-External-Oscillator
PH0-OSC_IN\ (PH0).Signal=RCC_OSC_IN
PH1-OSC_OUT\ (PH1).Mode=HSE-External-Oscillator
PH1-OSC_OUT\ (PH1).Signal=RCC_OSC_OUT
RCC.SYSCLKFreq_VALUE=480000000
RCC.SYSCLKSource=RCC_SYSCLKSOURCE_PLLCLK
board=custom
